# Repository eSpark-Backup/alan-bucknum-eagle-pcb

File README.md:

# Eagle PCB Design Optimization
#### Alan Bucknum

## Project Requirements
The existing Eagle files are present at [this link](https://github.com/eSpark-Consultants/alanbucknum-eaglepcb/tree/main/docs/Client-Files/Original-Design) (at the docs folder in the repository). The updated design files for v1.1 are also present in Design-Files folder.  Below changes are to be applied on Design-Files folder:
- The two buttons (SW1 & SW2) to be moved to the backside. Ideally SW1 & SW2 would be centered (top/bottom), and closer to the right-hand side
- The PCB length (currently 40mm) should be 20mm or less.
- Width is made as small as possible while maintaining technical accuracy and considerations.
- ~The micro-USB port to either be on one of the thin edges, or at least outside of the middle 25mm.~
- LED D9 can be fully removed.
- ~TAG-ICSP would ideally be centered (as much as possible).~
- Remove TP D7_ACCEL & TP GND.
- Remove: LDO and RCHRG Circuit.
- Remove: RFM69 & Antenna.
- Remove: USB Type C, ICSP Pins.
- Remove: AVR MCU.
- Replace: LEDs with 3mm TH IR LEDs.
- Replace: MCU with SEEEDSTUDIO ESP32C6
- Add: Additional IR Driver.

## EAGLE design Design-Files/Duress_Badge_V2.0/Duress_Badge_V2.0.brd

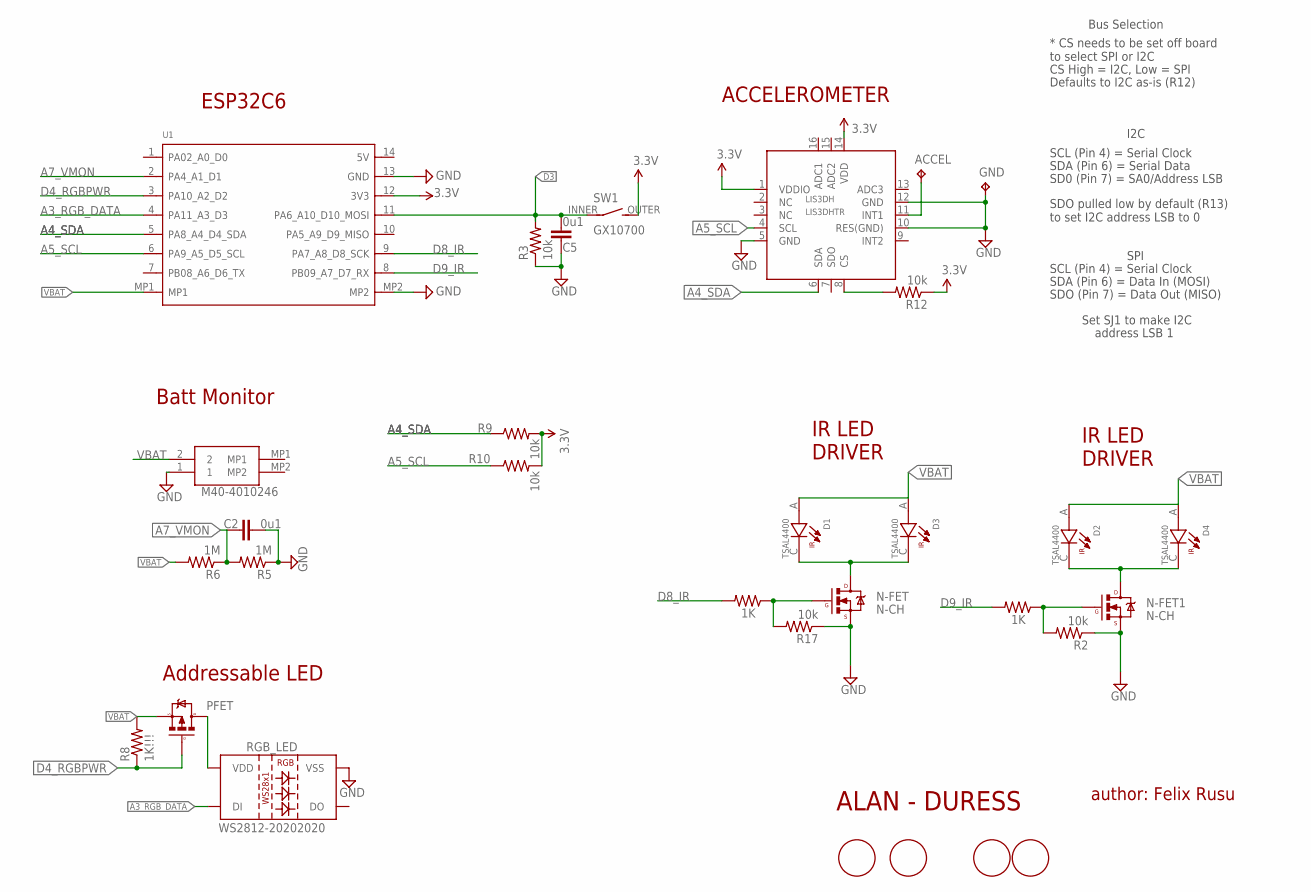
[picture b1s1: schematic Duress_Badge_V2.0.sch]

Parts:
ACCEL: TPB2,54; B2,54
BR_FIDUCIAL: FIDUCIAL1.5MM; FIDUCIAL_1.5MM
C2, C5: 0u1; 0603-CAP
D1, D2, D3, D4: TSAL4400; LEDRD254W45D335H610
FIDUCIAL_BOTTOMRIGHT: FIDUCIALSQ; FIDUCIAL_1.5MM_SQ
FIDUCIAL_TOPLEFT: FIDUCIALSQ; FIDUCIAL_1.5MM_SQ
GND: TPB2,54; B2,54
JST1: M40-4010246; M404010246
LIS3DH: LIS3DHTR; LGA16_3X3MM
N-FET, N-FET1: N-CH; SOT23-3
PFET: MOSFET-PCHANNELSMD; SOT23-3
R1, R4: 1K; 0603-RES
R2, R3, R9, R10, R12, R17: 10k; 0603-RES
R5, R6: 1M; 0603-RES
R8: 1K!!!; 0603-RES
RGB_LED: WS2812-20202020; WS2812-2020
SW1: GX10700
TL_FIDUCIAL: FIDUCIAL1.5MM; FIDUCIAL_1.5MM
U1: MOUDLE-SEEEDUINO-XIAO; MOUDLE14P-2.54-21X17.8MM

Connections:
A3_RGB_DATA: RGB_LED.3 (DI), U1.4 (PA11_A3_D3)
A4_SDA: LIS3DH.6 (SDA), R9.1, U1.5 (PA8_A4_D4_SDA)
A5_SCL: LIS3DH.4 (SCL), R10.1, U1.6 (PA9_A5_D5_SCL)
A7_VMON: C2.1, R5.2, R6.1, U1.2 (PA4_A1_D1)
D3: C5.2, R3.2, SW1.INNER, U1.11 (PA6_A10_D10_MOSI)
D4_RGBPWR: PFET.1 (G), R8.1, U1.3 (PA10_A2_D2)
D7_ACCEL: ACCEL.TP, LIS3DH.11 (INT1)
D8_IR: R4.2, U1.9 (PA7_A8_D8_SCK)
D9_IR: R1.2, U1.8 (PB09_A7_D7_RX)
GND: C2.2, C5.1, GND.TP, JST1.1, LIS3DH.5 (GND), LIS3DH.10 (RES(GND)), LIS3DH.12 (GND), N-FET.2 (S), N-FET1.2 (S), R2.1, R3.1, R5.1, R17.1, RGB_LED.2 (VSS), U1.13 (GND), U1.MP2
unnamed: D1.C, D3.C, N-FET.3 (D)
unnamed: N-FET1.1 (G), R1.1, R2.2
unnamed: D2.C, D4.C, N-FET1.3 (D)
unnamed: PFET.3 (D), RGB_LED.4 (VDD)
unnamed: N-FET.1 (G), R4.1, R17.2
unnamed: LIS3DH.8 (CS), R12.2
VBAT: D1.A, D2.A, D3.A, D4.A, JST1.2, PFET.2 (S), R6.2, R8.2, U1.MP1
VCC: LIS3DH.1 (VDDIO), LIS3DH.14 (VDD), R9.2, R10.2, R12.1, SW1.OUTER (S), U1.12 (3V3)

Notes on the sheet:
ALAN - DURESS
author: Felix Rusu
I2C
SCL (Pin 4) = Serial Clock
SDA (Pin 6) = Serial Data
SD0 (Pin 7) = SA0/Address LSB
* CS needs to be set off board to select SPI or I2C
CS High = I2C, Low = SPI
Defaults to I2C as-is (R12)
SDO pulled low by default (R13) to set I2C address LSB to 0
Bus Selection
SPI
SDA (Pin 6) = Data In (MOSI)
SDO (Pin 7) = Data Out (MISO)
Set SJ1 to make I2C
address LSB 1
Batt Monitor
ACCELEROMETER
IR LED DRIVER
ESP32C6
Addressable LED

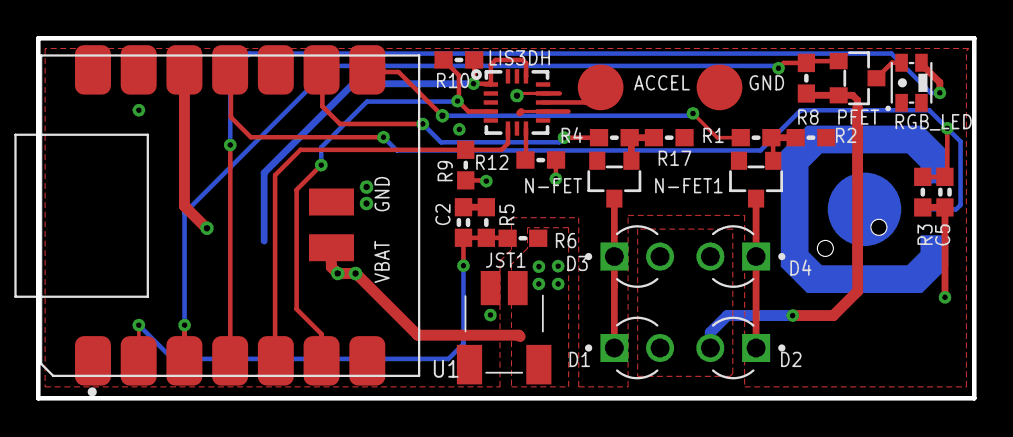
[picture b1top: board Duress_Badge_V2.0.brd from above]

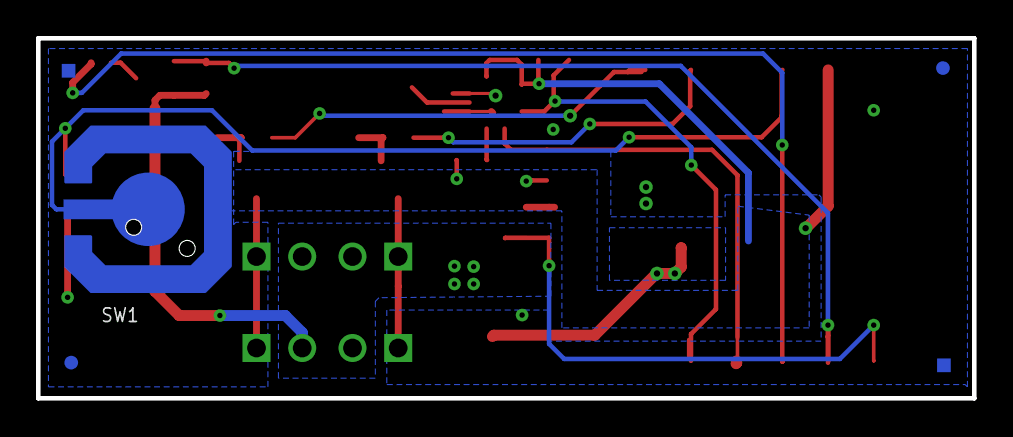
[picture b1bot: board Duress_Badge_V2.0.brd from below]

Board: 2 copper layers, 52.0 x 20.0 mm, 31 parts (5 on the bottom side), 18 nets.

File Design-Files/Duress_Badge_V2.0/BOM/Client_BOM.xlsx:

| # | Item Type | Designator | Description | Footprint | Manufacturer Part Number | Manufacturer | Comment | Quantity | Remarks
 | 1 | Capacitor | C2, C5 | 0.1uF Capacitor | CAP0603-CAP | - | - | 0.1uF | 2
 | 2 | Resistor | R2, R3, R9, R10, R12, R17 | 10K Resistor | RESISTOR0603 | - | - | 10K | 6
 | 3 | Resistor | R1, R4,R8 | 1K Resistor | RESISTOR0603 | - | - | 1K | 3
 | 4 | Resistor | R5, R6 | 1M Resistor | RESISTOR0603 | - | - | 1M | 2
 | 5 | Switch | SW1 | - | custom | GX10700 | Snaptron | - | 1
 | 6 | Header | JST1 | Headers & Wire Housings 2P SIL SMT HORIZ SHROUDED TAB HEADER | custom | M40-4010246 | Harwin Inc. | - | 1
 | 7 | Mosfet | PFET | P-Channel Mosfet | SOT23-3 | - | - | - | 1
 | 8 | Mosfet | N-FET, N-FET1 | N-Channel Mosfet | SOT23-3 | - | - | - | 2
 | 9 | IR LED | D1, D2, D3, D4 | IR LED | custom | TSAL4400 | Vishay Semiconductor Opto Division | - | 4
 | 10 | RGB LED | RGB_LED | RGB LED | custom | WS2812-20202020 | Worldsemi | - | 1
 | 11 | IC | LIS3DH | 3-Axis Accelerometer with I2C/SPI Interface | custom | LIS3DHTR | STMicroelectronics | - | 1
 | 12 | Module | U2 | MOUDLE-SEEEDUINO-XIAO MOUDLE14P-2.54-21X17.8MM | custom | ESP32-C6 | Saeed Studio | - | 1
 | 13 | Test Point | ACCEL, GND | Test point | custom | - | - | - | 2
 | 14 | FIDUCIAL1.5MM | BR_FIDUCIAL, TL_FIDUCIAL | Fiducial Marker |  | - | - | - | 2
 | 15 | FIDUCIAL1.5MFIDUCIALSQM | FIDUCIAL_BOTTOMRIGHT, FIDUCIAL_TOPLEFT | Fiducial Marker |  | - | - | - | 2

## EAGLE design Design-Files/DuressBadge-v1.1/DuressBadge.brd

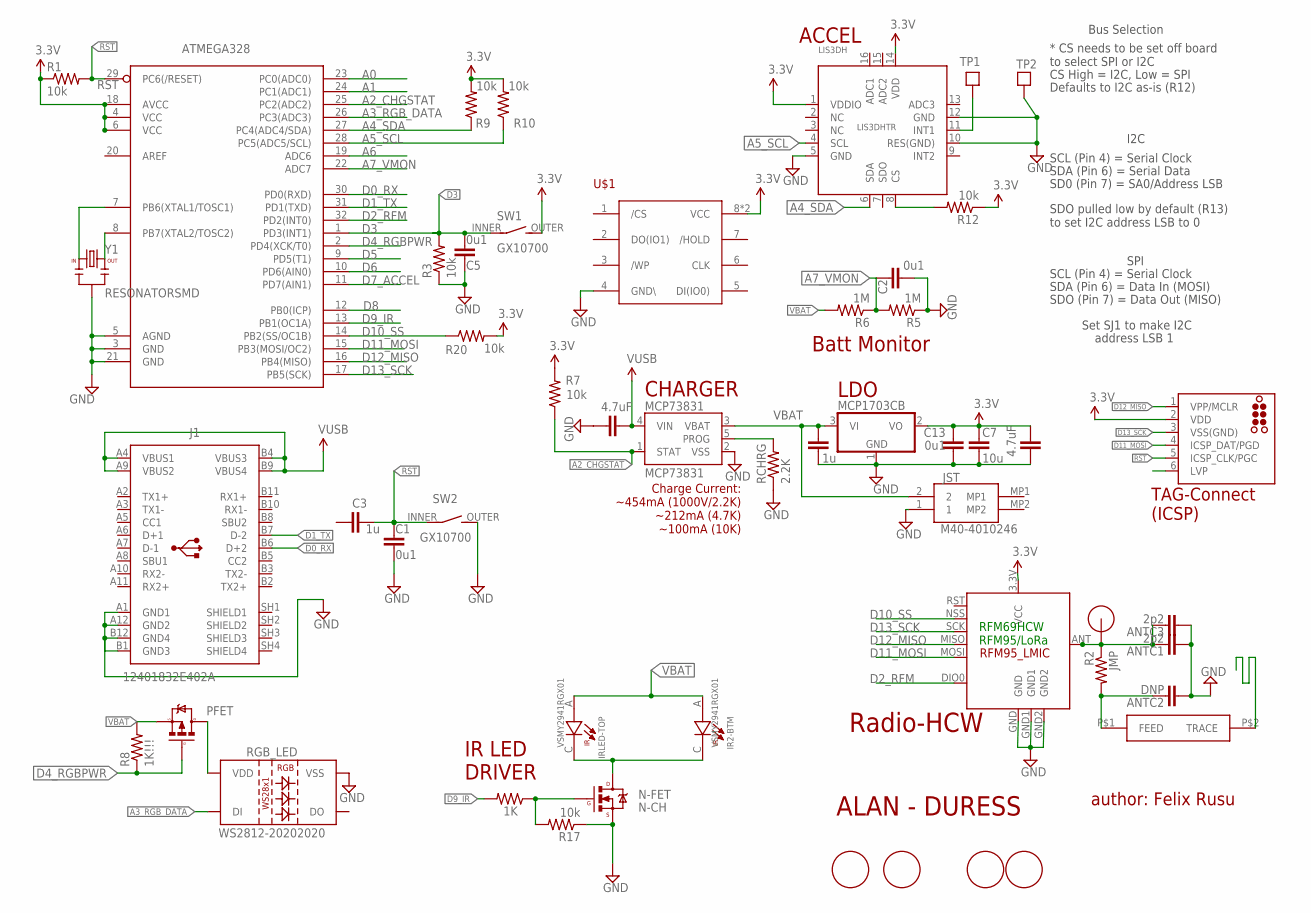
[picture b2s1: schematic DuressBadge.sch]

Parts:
ANTC1: 2p2; 0603-CAP
ANTC2: DNP; 0402-CAP
ANTC3: 2p2; 0402-CAP
ATMEGA328: ATMega-328; TQFP32-08
BR_FIDUCIAL: FIDUCIAL1.5MM; FIDUCIAL_1.5MM
C1, C2, C5, C13: 0u1; 0603-CAP
C3, C14: 1u; 0603-CAP
C4, C8: 4.7uF; 0603-CAP
C7: 10u; 0805-CAP
FIDUCIAL_BOTTOMRIGHT: FIDUCIALSQ; FIDUCIAL_1.5MM_SQ
FIDUCIAL_TOPLEFT: FIDUCIALSQ; FIDUCIAL_1.5MM_SQ
IR2-BTM: VSMY2941RGX01; DIO_VSMY2941RGX01
IRLED-TOP: VSMY2941RGX01; DIO_VSMY2941RGX01
J1: 12401832E402A
JST: M40-4010246; M404010246
LDO: MCP1703CB; SOT23
LIS3DH: LIS3DHTR; LGA16_3X3MM
MCP73831: MCP73831; SOT23-5
N-FET: N-CH; SOT23-3
PFET: MOSFET-PCHANNELSMD; SOT23-3
R1, R3, R7, R9, R10, R12, R17, R20: 10k; 0603-RES
R2: JMP; 0402-RES
R4: 1K; 0603-RES
R5, R6: 1M; 0603-RES
R8: 1K!!!; 0603-RES
RCHRG: 2.2K; 0603-RES
RGB_LED: WS2812-20202020; WS2812-2020
SW1, SW2: GX10700
TAG-ICSP: TAG-Connect; TC2030-MCP-NL
TL_FIDUCIAL: FIDUCIAL1.5MM; FIDUCIAL_1.5MM
TP1, TP2: PAD_OR_PIN_1TP; PAD_1_TESTPOINT
U$1: RFM12B_ANTENNA; ANTENNA_THRUHOLE
U$2: W25Q40CLSNIG; USON
U$5: JOHANSON0900AT43A0070
U$11: RFM95_WITHRST; RFM95_LONGER_WITHRST
Y1: RESONATORSMD; RESONATOR-SMD

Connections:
A0: ATMEGA328.23 (PC0(ADC0))
A1: ATMEGA328.24 (PC1(ADC1))
A2_CHGSTAT: ATMEGA328.25 (PC2(ADC2)), MCP73831.1 (STAT), R7.1
A3_RGB_DATA: ATMEGA328.26 (PC3(ADC3)), RGB_LED.3 (DI)
A4_SDA: ATMEGA328.27 (PC4(ADC4/SDA)), LIS3DH.6 (SDA), R9.1
A5_SCL: ATMEGA328.28 (PC5(ADC5/SCL)), LIS3DH.4 (SCL), R10.1
A6: ATMEGA328.19 (ADC6)
A7_VMON: ATMEGA328.22 (ADC7), C2.1, R5.2, R6.1
ANT: ANTC1.2, ANTC3.2, R2.1, U$1.P$1, U$11.ANT
D0_RX: ATMEGA328.30 (PD0(RXD)), J1.B6 (D+2)
D1_TX: ATMEGA328.31 (PD1(TXD)), J1.B7 (D-2)
D2_RFM: ATMEGA328.32 (PD2(INT0)), U$11.DIO0
D3: ATMEGA328.1 (PD3(INT1)), C5.2, R3.2, SW1.INNER
D4_RGBPWR: ATMEGA328.2 (PD4(XCK/T0)), PFET.1 (G), R8.1
D5: ATMEGA328.9 (PD5(T1))
D6: ATMEGA328.10 (PD6(AIN0))
D7_ACCEL: ATMEGA328.11 (PD7(AIN1)), LIS3DH.11 (INT1), TP1.TP
D8: ATMEGA328.12 (PB0(ICP))
D9_IR: ATMEGA328.13 (PB1(OC1A)), R4.2
D10_SS: ATMEGA328.14 (PB2(SS/OC1B)), R20.1, U$11.NSS (SEL)
D11_MOSI: ATMEGA328.15 (PB3(MOSI/OC2)), TAG-ICSP.4 (ICSP_DAT/PGD), U$11.MOSI
D12_MISO: ATMEGA328.16 (PB4(MISO)), TAG-ICSP.1 (VPP/MCLR), U$11.MISO
D13_SCK: ATMEGA328.17 (PB5(SCK)), TAG-ICSP.3 (VSS(GND)), U$11.SCK
GND: ANTC1.1, ANTC2.1, ANTC3.1, ATMEGA328.3 (GND), ATMEGA328.5 (AGND), ATMEGA328.21 (GND), C1.1, C2.2, C4.1, C5.1, C7.2, C8.1, C13.2, C14.2, J1.A1 (GND1), J1.A12 (GND2), J1.B1 (GND3), J1.B12 (GND4), JST.1, LDO.1 (GND), LIS3DH.5 (GND), LIS3DH.10 (RES(GND)), LIS3DH.12 (GND), MCP73831.2 (VSS), N-FET.2 (S), R3.1, R5.1, R17.1, RCHRG.1, RGB_LED.2 (VSS), SW2.OUTER (S), TAG-ICSP.6 (LVP), TP2.TP, U$2.4 (GND\), U$11.GND, U$11.GND1, U$11.GND2, Y1.XTAL2_GND
unnamed: ATMEGA328.7 (PB6(XTAL1/TOSC1)), Y1.XTAL1_IN
unnamed: IR2-BTM.C, IRLED-TOP.C, N-FET.3 (D)
unnamed: MCP73831.5 (PROG), RCHRG.2
unnamed: PFET.3 (D), RGB_LED.4 (VDD)
unnamed: N-FET.1 (G), R4.1, R17.2
unnamed: ANTC2.2, R2.2, U$5.P$1 (FEED)
unnamed: LIS3DH.8 (CS), R12.2
unnamed: ATMEGA328.8 (PB7(XTAL2/TOSC2)), Y1.XTAL3_OUTPUT (XTAL3_OUT)
RST: ATMEGA328.29 (PC6(/RESET)), C1.2, C3.2, R1.2, SW2.INNER, TAG-ICSP.5 (ICSP_CLK/PGC)
VBAT: C14.1, IR2-BTM.A, IRLED-TOP.A, JST.2, LDO.3 (VI), MCP73831.3 (VBAT), PFET.2 (S), R6.2, R8.2
VCC: ATMEGA328.4 (VCC), ATMEGA328.6 (VCC), ATMEGA328.18 (AVCC), C4.2, C7.1, C13.1, LDO.2 (VO), LIS3DH.1 (VDDIO), LIS3DH.14 (VDD), R1.1, R7.2, R9.2, R10.2, R12.1, R20.2, SW1.OUTER (S), TAG-ICSP.2 (VDD), U$2.8 (VCC), U$2.GND1 (VCC), U$11.3.3V (VCC)
VUSB: C8.2, J1.A4 (VBUS1), J1.A9 (VBUS2), J1.B4 (VBUS3), J1.B9 (VBUS4), MCP73831.4 (VIN)

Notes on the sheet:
ALAN - DURESS
author: Felix Rusu
I2C
SCL (Pin 4) = Serial Clock
SDA (Pin 6) = Serial Data
SD0 (Pin 7) = SA0/Address LSB
* CS needs to be set off board to select SPI or I2C
CS High = I2C, Low = SPI
Defaults to I2C as-is (R12)
SDO pulled low by default (R13) to set I2C address LSB to 0
Bus Selection
SPI
SDA (Pin 6) = Data In (MOSI)
SDO (Pin 7) = Data Out (MISO)
Set SJ1 to make I2C
address LSB 1
Batt Monitor
Charge Current: ~454mA (1000V/2.2K) ~212mA (4.7K) ~100mA (10K)
CHARGER
ACCEL
RFM69HCW RFM95/LoRa
TAG-Connect (ICSP)
Radio-HCW
IR LED DRIVER

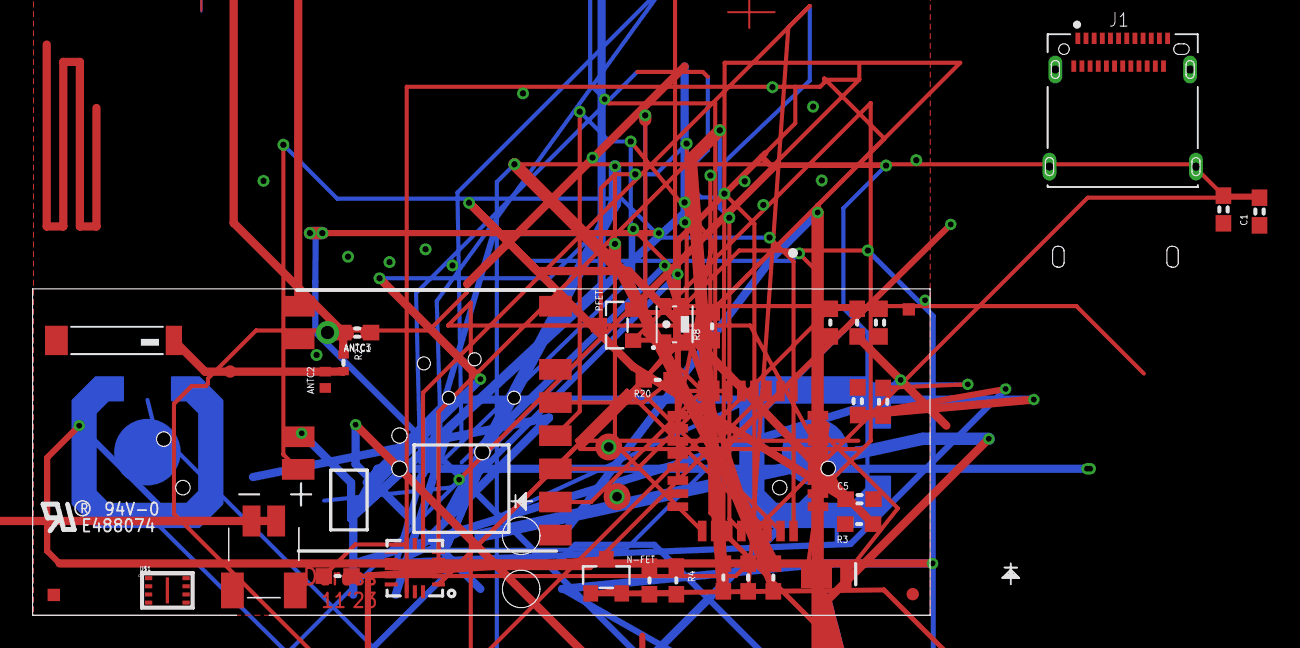
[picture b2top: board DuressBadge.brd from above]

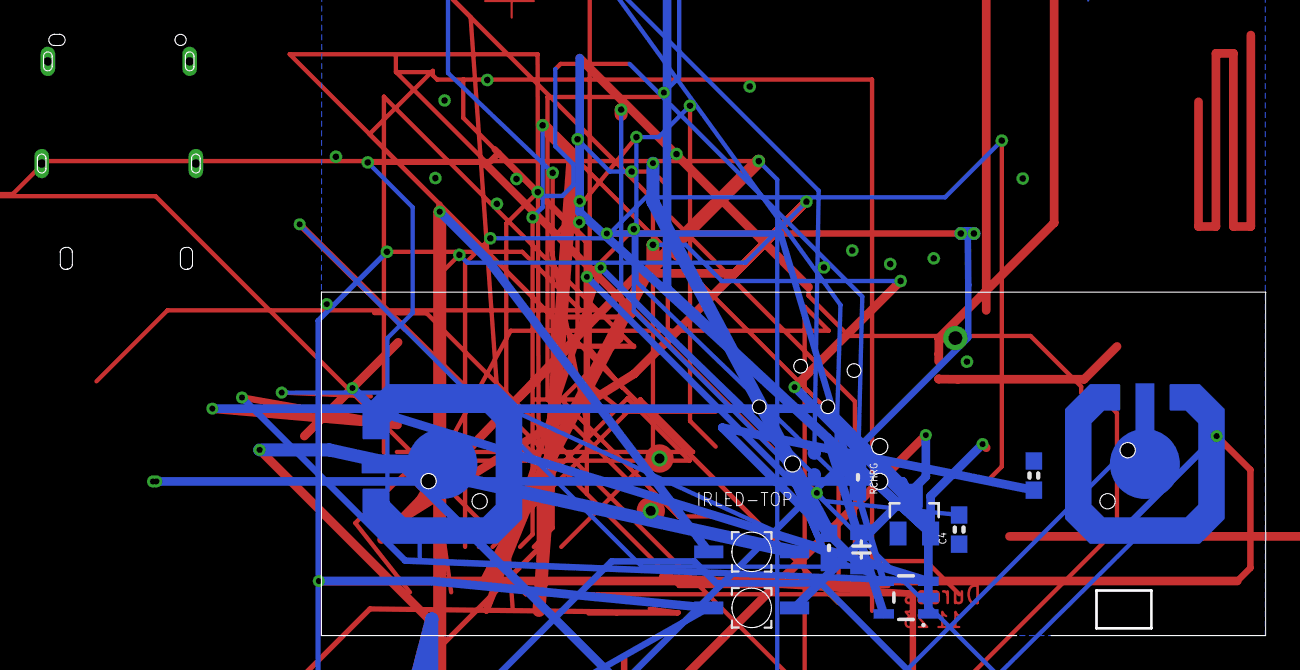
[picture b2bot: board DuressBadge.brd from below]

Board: 2 copper layers, 71.4 x 34.9 mm, 52 parts (12 on the bottom side), 30 nets.

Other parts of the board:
U$31: LOGO_UL_XSMALL_PCBWAY

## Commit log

2025-03-13 Add: Client original design
2025-03-13 Add: Working folder
2025-03-19 Change: folder structure
2025-03-20 Add: gitignore; Remove: temp files
2025-03-21 Update PRD - v2
2025-03-21 pdf generated for Schematic design v1.1
2025-03-21 #1 Schematic in Progress
2025-03-24 #1 Schematic completed
2025-03-24 Remove: v1.1 schematic PDF
2025-03-24 Remove: temp files
2025-03-24 #1 Placement in progress
2025-03-25 #1 Routing in progress
2025-03-26 #1 updated schematic
2025-03-26 # Pull up resistors added and PCB completed
2025-03-26 #1 Some changes in routing
2025-03-29 #1 Pads added and Deliverables generated

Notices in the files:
parts and their libraries:
microbuilder: This work is placed in the public domain, and may be freely used for commercial and non-commercial work with the following conditions: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
SparkFun-PowerIC: Licensing: Creative Commons ShareAlike 4.0 International - https://creativecommons.org/licenses/by-sa/4.0
